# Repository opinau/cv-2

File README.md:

# OPINAU-FILLER-CV-2

Europska unija

Zajedno do fondova EU

Projekt je sufinancirala Europska unija iz Europskog fonda za regionalni razvoj

[**Inovacijski vaučeri za MSP-ove**](https://efondovi.mrrfeu.hr/MISCms/Pozivi/Poziv?id=cfc4e79b-68c5-4ce8-a481-04ee5d76dda2)

Operativni program: **Konkurentnost i Kohezija 2014. - 2020.**

Naziv projekta: **OPINAU-FILLER-CV-2**

OPINAU-FILLER-CV-2 projekt odnosi se na razvoj sklopovlja i popratne programske podrške (unutar Python/C++/ROS okruženja) za prototip sustava za beskontaktno mjerenje razine tekućine u boci prilikom punjenja u open-source punionici piva temeljen na principima računalnog vida sa mogućim odstupanjima od maksimalno 10%.

Partneri na projektu: [**Open Book d.o.o.**](https://www.openbook.hr/) i [**Fakultet elektrotehnike, strojarstva i brodogradnje Sveučilišta u Splitu**](https://www.fesb.unist.hr/)

Ukupna vrijednost projekta: **72.000,00 HRK**

Iznos koji sufinancira EU: **54.000,00 HRK**

Razdoblje provedbe projekta: **09.08.2021. - 03.12.2021.**

Kontakt osoba: **Igor Cota**

---
Repozitorij se sastoji od dva modula:
1. OpenMV modul
2. RaspberryPi modul
---
Prije korištenja pročitajte [dokumentaciju](report/openBookIzvjestaj_ver_4.pdf).

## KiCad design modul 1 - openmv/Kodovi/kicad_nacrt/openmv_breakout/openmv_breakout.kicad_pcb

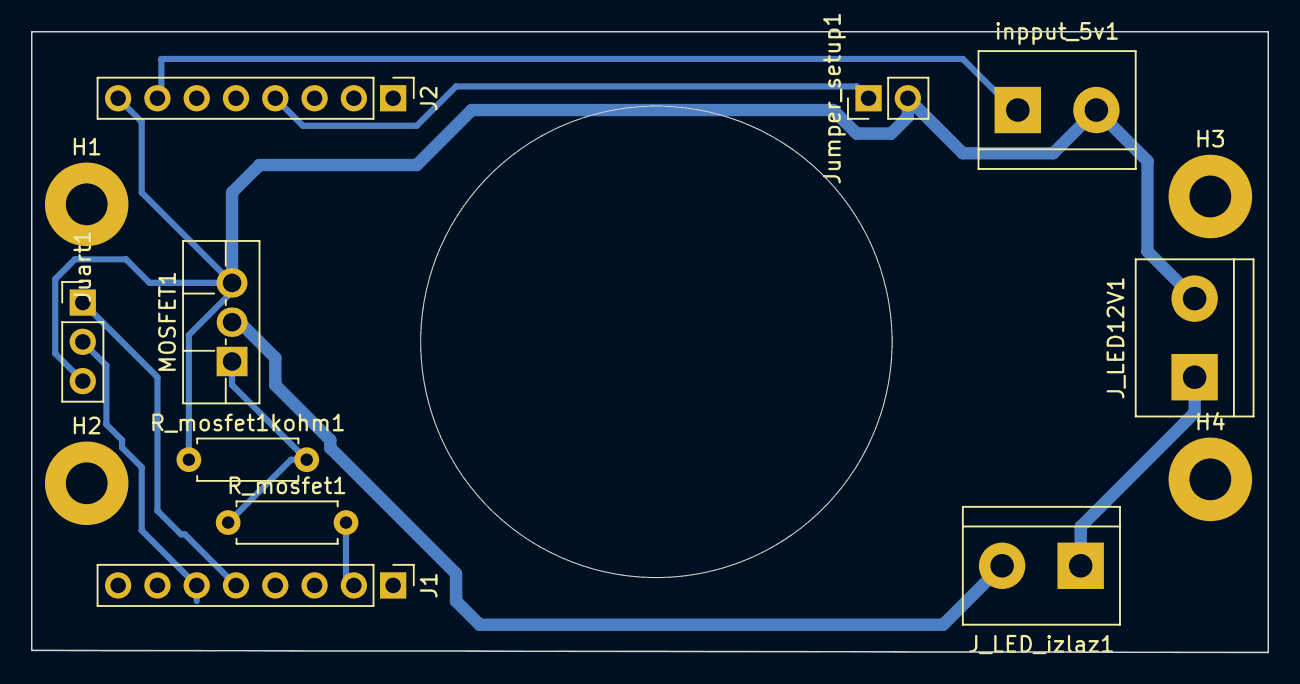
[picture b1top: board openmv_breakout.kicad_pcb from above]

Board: 2 copper layers, 79.9 x 40.1 mm, 14 parts (0 on the bottom side), 9 nets.

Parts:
H1, H2, H3, H4: MountingHole; MountingHole_2.7mm_Pad
J1, J2: Conn_01x08_Male; PinHeader_1x08_P2.54mm_Vertical
J_LED12V1: Conn_01x02_Female; TerminalBlock_bornier-2_P5.08mm
J_LED_izlaz1: Conn_01x02_Female; TerminalBlock_bornier-2_P5.08mm
Juart1: Conn_01x03_Female; PinHeader_1x03_P2.54mm_Vertical
Jumper_setup1: Conn_01x02_Male; PinHeader_1x02_P2.54mm_Vertical
MOSFET1: IRLIZ44N; TO-220F-3_Vertical
R_mosfet1, R_mosfet1kohm1: R; R_Axial_DIN0207_L6.3mm_D2.5mm_P7.62mm_Horizontal
inpput_5v1: Conn_01x02_Female; TerminalBlock_bornier-2_P5.08mm

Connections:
5vin: J2.7, inpput_5v1.1
12V+: J_LED12V1.1, J_LED_izlaz1.1
DRAIN: J_LED_izlaz1.2, MOSFET1.2
GATE: MOSFET1.1, R_mosfet1.1, R_mosfet1kohm1.2
GND: J2.8, J_LED12V1.2, Juart1.3, Jumper_setup1.2, MOSFET1.3, R_mosfet1kohm1.1, inpput_5v1.2
P4: J1.2, R_mosfet1.2
P9: J2.4, Jumper_setup1.1
rx: J1.6, Juart1.2
tx: J1.5, Juart1.1
